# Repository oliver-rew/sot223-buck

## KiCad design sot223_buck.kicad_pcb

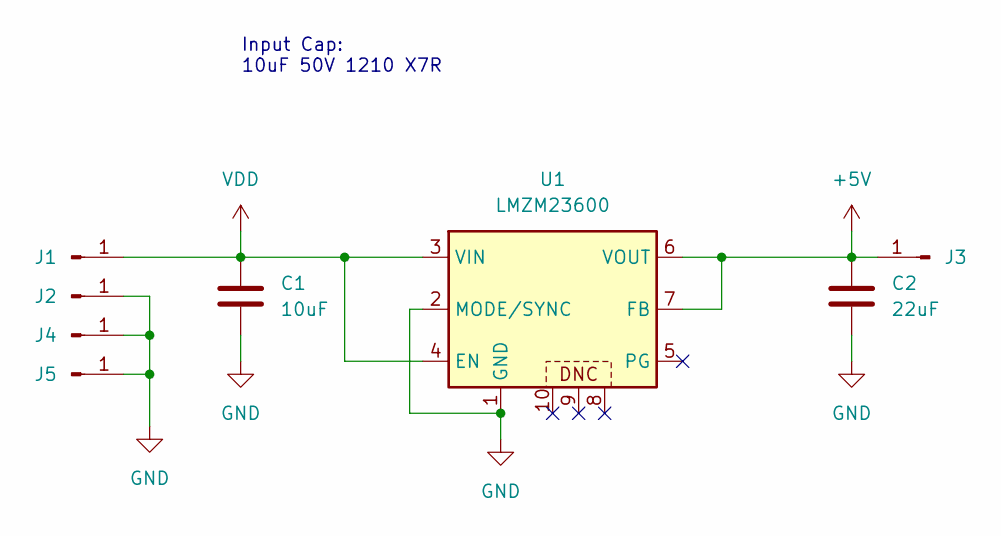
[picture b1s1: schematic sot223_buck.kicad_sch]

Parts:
C1: 10uF; C_0805_2012Metric
C2: 22uF; C_0805_2012Metric
J1, J2, J3, J4, J5: Conn_01x01_Pin; TestPoint_THTPad_D1.5mm_Drill0.7mm
U1: LMZM23600; Texas_SIL0010A_MicroSiP-10-1EP_3.8x3mm_P0.6mm_EP0.7x2.9mm_T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

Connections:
+5V: C2.1, J3.1, U1.6 (VOUT), U1.7 (FB)
GND: C1.2, C2.2, J2.1, J4.1, J5.1, U1.1 (GND), U1.2 (MODE/SYNC), U1.11 (GND)
VDD: C1.1, J1.1, U1.3 (VIN), U1.4 (EN)

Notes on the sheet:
Input Cap: 10uF 50V 1210 X7R

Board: 2 copper layers, 8 parts (0 on the bottom side), 3 nets, no tracks yet.

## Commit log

2024-06-23 feat: add files
